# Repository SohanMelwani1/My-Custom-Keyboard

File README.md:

# My-Custom-Keyboard
My own Custom 60% Mechanical Keyboard

BOM link: https://docs.google.com/spreadsheets/d/1pmS31pF6GHp4k1bNOez-trRHEgPxX3IoW4xAfGn9qzQ/edit?gid=0#gid=0

# Features
- 3 Macros
- Anti-Ghosting
- customizable keycaps and switches
- swappable switches without needing to re-solder it
- 60% mechanical keyboard
- no screws required
- 3d printed case
- Matrix layout
- 61 keys

___

While making this I learnt How Matrix keyboards work, types of mounting of keyboards, Schematic and how to use it, PCB wiring, importing pcb to fusion and creating case, Firmware and about keyboards in general, this was my first PCB I have ever designed. I added 4 holes in each corner of the case to secure the pieces into place.

___

PCB without ground

PCB

PCB 3d view

Schematic stabilizers and mounting hole

Schematic RaspberryPi_Pico

Schematic Matrix with switches and diodes

Full schematic

Full 3d model

3d model case, plate and top frame

3d model case 

3d model plate

3d model top frame

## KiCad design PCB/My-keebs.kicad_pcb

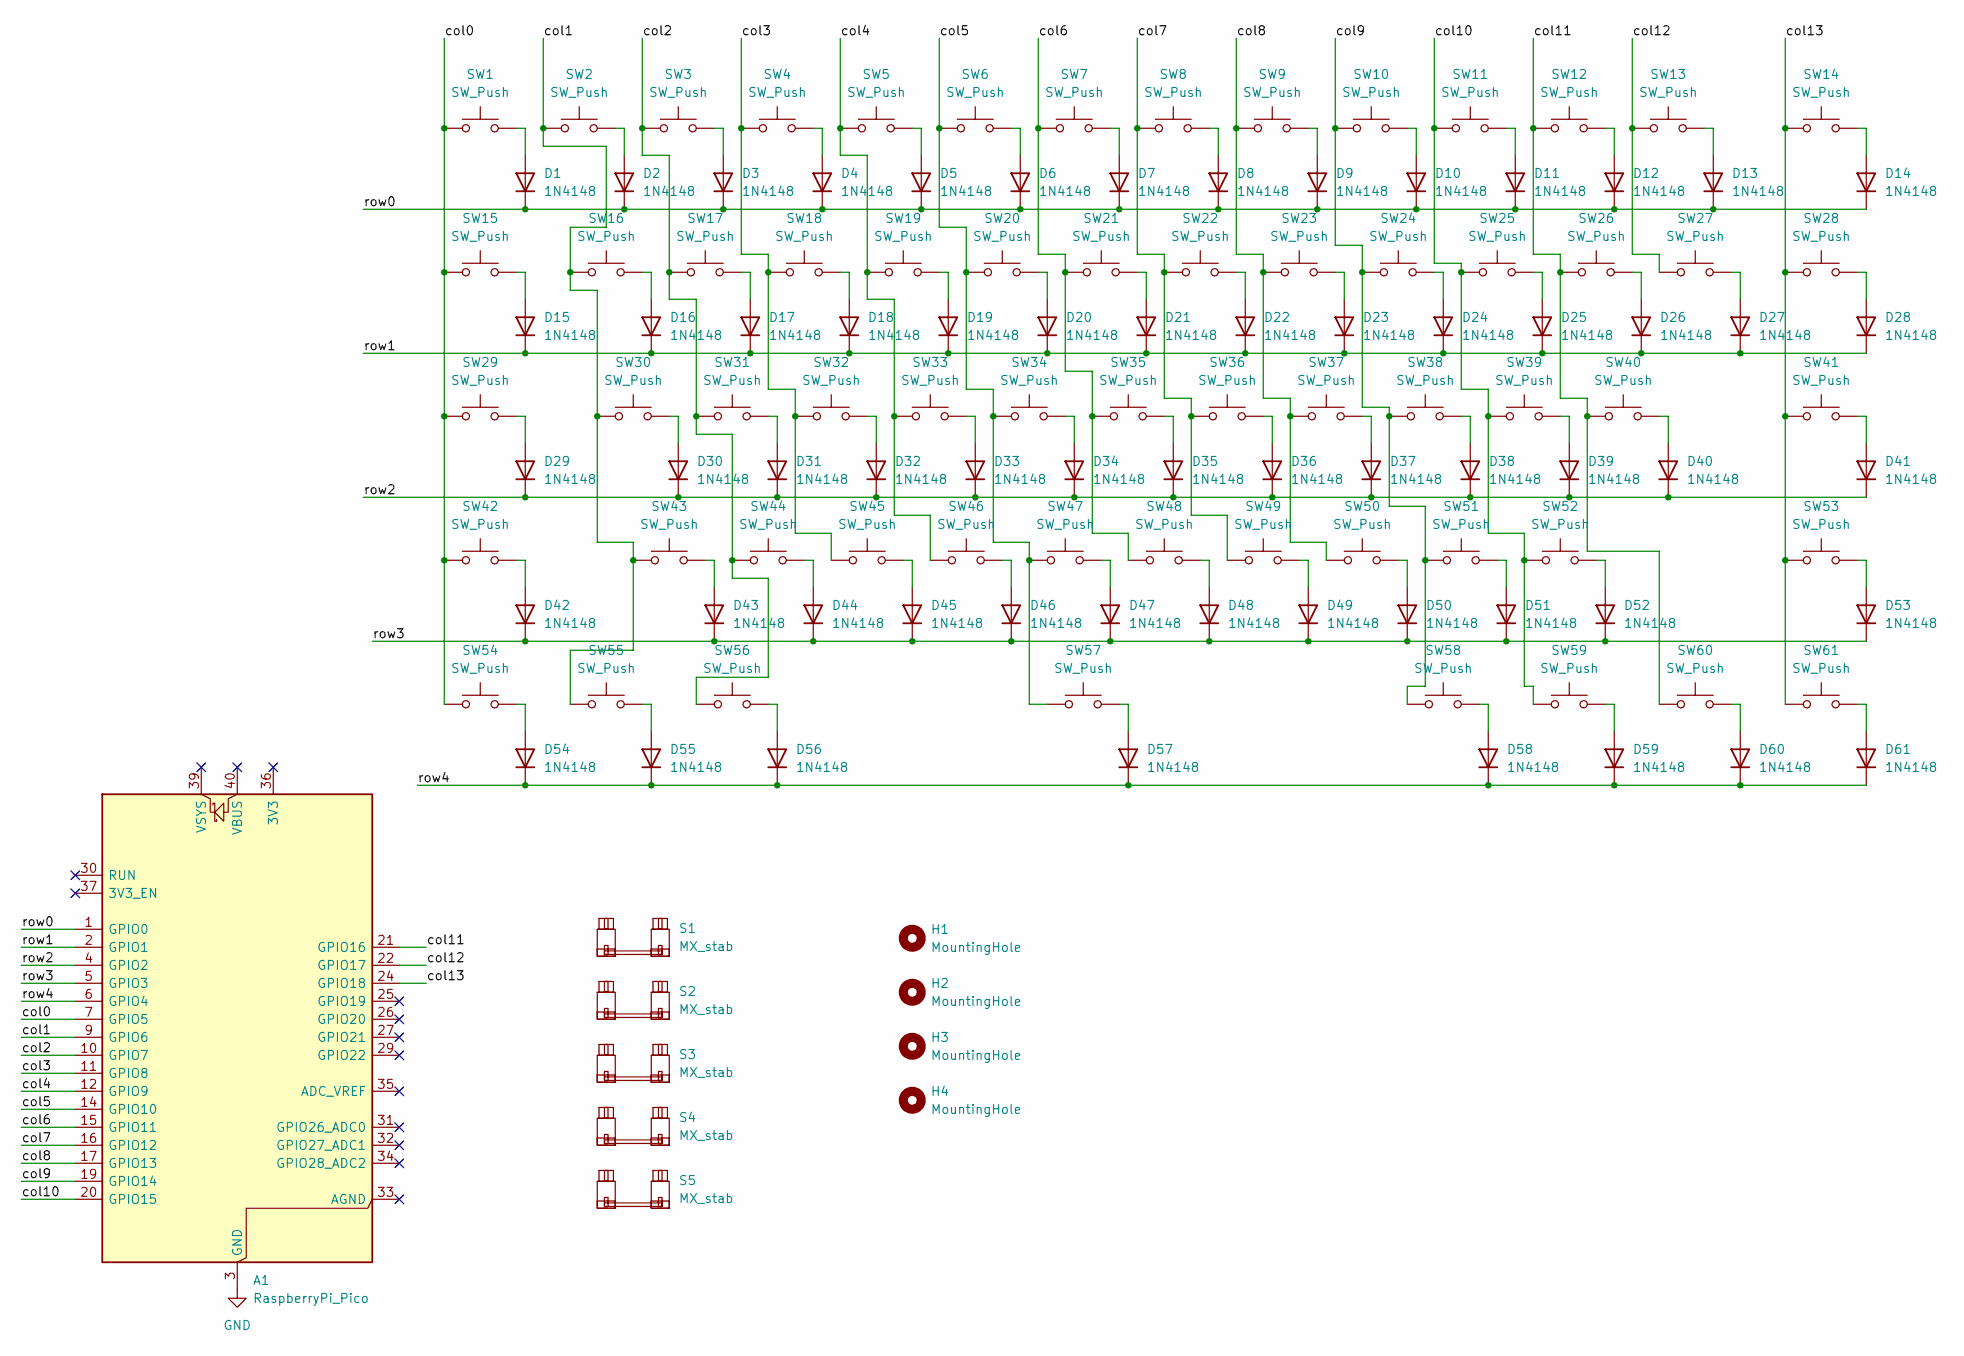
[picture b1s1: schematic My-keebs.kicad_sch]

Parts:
A1: RaspberryPi_Pico; RaspberryPi_Pico_Common_THT
D1, D2, D3, D4, D5, D6, D7, D8, D9, D10, D11, D12, D13, D14, D15, D16, D17, D18, D19, D20, D21, D22, D23, D24, D25, D26, D27, D28, D29, D30, D31, D32, D33, D34, D35, D36, D37, D38, D39, D40, D41, D42, D43, D44, D45, D46, D47, D48, D49, D50, D51, D52, D53, D54, D55, D56, D57, D58, D59, D60, D61: 1N4148; D_DO-35_SOD27_P7.62mm_Horizontal
H1, H2, H3, H4: MountingHole; MountingHole_3.2mm_M3
S1, S2, S3, S5: MX_stab; STAB_MX_2u
S4: MX_stab; STAB_MX_6.25u
SW1, SW2, SW3, SW4, SW5, SW6, SW7, SW8, SW9, SW10, SW11, SW12, SW13, SW14, SW15, SW16, SW17, SW18, SW19, SW20, SW21, SW22, SW23, SW24, SW25, SW26, SW27, SW28, SW29, SW30, SW31, SW32, SW33, SW34, SW35, SW36, SW37, SW38, SW39, SW40, SW41, SW42, SW43, SW44, SW45, SW46, SW47, SW48, SW49, SW50, SW51, SW52, SW53, SW54, SW55, SW56, SW57, SW58, SW59, SW60, SW61: SW_Push; SW_MX_1u

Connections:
/col0: A1.7 (GPIO5), SW1.1, SW15.1, SW29.1, SW42.1, SW54.1
/col1: A1.9 (GPIO6), SW2.1, SW16.1, SW30.1, SW43.1, SW55.1
/col2: A1.10 (GPIO7), SW3.1, SW17.1, SW31.1, SW44.1, SW56.1
/col3: A1.11 (GPIO8), SW4.1, SW18.1, SW32.1, SW45.1
/col4: A1.12 (GPIO9), SW5.1, SW19.1, SW33.1, SW46.1
/col5: A1.14 (GPIO10), SW6.1, SW20.1, SW34.1, SW47.1, SW57.1
/col6: A1.15 (GPIO11), SW7.1, SW21.1, SW35.1, SW48.1
/col7: A1.16 (GPIO12), SW8.1, SW22.1, SW36.1, SW49.1
/col8: A1.17 (GPIO13), SW9.1, SW23.1, SW37.1, SW50.1
/col9: A1.19 (GPIO14), SW10.1, SW24.1, SW38.1, SW51.1, SW58.1
/col10: A1.20 (GPIO15), SW11.1, SW25.1, SW39.1, SW52.1, SW59.1
/col11: A1.21 (GPIO16), SW12.1, SW26.1, SW40.1, SW60.1
/col12: A1.22 (GPIO17), SW13.1, SW27.1
/col13: A1.24 (GPIO18), SW14.1, SW28.1, SW41.1, SW53.1, SW61.1
/row0: A1.1 (GPIO0), D1.1 (K), D2.1 (K), D3.1 (K), D4.1 (K), D5.1 (K), D6.1 (K), D7.1 (K), D8.1 (K), D9.1 (K), D10.1 (K), D11.1 (K), D12.1 (K), D13.1 (K), D14.1 (K)
/row1: A1.2 (GPIO1), D15.1 (K), D16.1 (K), D17.1 (K), D18.1 (K), D19.1 (K), D20.1 (K), D21.1 (K), D22.1 (K), D23.1 (K), D24.1 (K), D25.1 (K), D26.1 (K), D27.1 (K), D28.1 (K)
/row2: A1.4 (GPIO2), D29.1 (K), D30.1 (K), D31.1 (K), D32.1 (K), D33.1 (K), D34.1 (K), D35.1 (K), D36.1 (K), D37.1 (K), D38.1 (K), D39.1 (K), D40.1 (K), D41.1 (K)
/row3: A1.5 (GPIO3), D42.1 (K), D43.1 (K), D44.1 (K), D45.1 (K), D46.1 (K), D47.1 (K), D48.1 (K), D49.1 (K), D50.1 (K), D51.1 (K), D52.1 (K), D53.1 (K)
/row4: A1.6 (GPIO4), D54.1 (K), D55.1 (K), D56.1 (K), D57.1 (K), D58.1 (K), D59.1 (K), D60.1 (K), D61.1 (K)
GND: A1.3 (GND), A1.8 (GND), A1.13 (GND), A1.18 (GND), A1.23 (GND), A1.28 (GND), A1.38 (GND)
unnamed: D1.2 (A), SW1.2
unnamed: D2.2 (A), SW2.2
unnamed: D3.2 (A), SW3.2
unnamed: D4.2 (A), SW4.2
unnamed: D5.2 (A), SW5.2
unnamed: D6.2 (A), SW6.2
unnamed: D7.2 (A), SW7.2
unnamed: D8.2 (A), SW8.2
unnamed: D9.2 (A), SW9.2
unnamed: D10.2 (A), SW10.2
unnamed: D11.2 (A), SW11.2
unnamed: D12.2 (A), SW12.2
unnamed: D13.2 (A), SW13.2
unnamed: D14.2 (A), SW14.2
unnamed: D15.2 (A), SW15.2
unnamed: D16.2 (A), SW16.2
unnamed: D17.2 (A), SW17.2
unnamed: D18.2 (A), SW18.2
unnamed: D19.2 (A), SW19.2
unnamed: D20.2 (A), SW20.2
unnamed: D21.2 (A), SW21.2
unnamed: D22.2 (A), SW22.2
unnamed: D23.2 (A), SW23.2
unnamed: D24.2 (A), SW24.2
unnamed: D25.2 (A), SW25.2
unnamed: D26.2 (A), SW26.2
unnamed: D27.2 (A), SW27.2
unnamed: D28.2 (A), SW28.2
unnamed: D29.2 (A), SW29.2
unnamed: D30.2 (A), SW30.2
unnamed: D31.2 (A), SW31.2
unnamed: D32.2 (A), SW32.2
unnamed: D33.2 (A), SW33.2
unnamed: D34.2 (A), SW34.2
unnamed: D35.2 (A), SW35.2
unnamed: D36.2 (A), SW36.2
unnamed: D37.2 (A), SW37.2
unnamed: D38.2 (A), SW38.2
unnamed: D39.2 (A), SW39.2
unnamed: D40.2 (A), SW40.2
unnamed: D41.2 (A), SW41.2
unnamed: D42.2 (A), SW42.2
unnamed: D43.2 (A), SW43.2
unnamed: D44.2 (A), SW44.2
unnamed: D45.2 (A), SW45.2
unnamed: D46.2 (A), SW46.2
unnamed: D47.2 (A), SW47.2
unnamed: D48.2 (A), SW48.2
unnamed: D49.2 (A), SW49.2
unnamed: D50.2 (A), SW50.2
unnamed: D51.2 (A), SW51.2
unnamed: D52.2 (A), SW52.2
unnamed: D53.2 (A), SW53.2
unnamed: D54.2 (A), SW54.2
unnamed: D55.2 (A), SW55.2
unnamed: D56.2 (A), SW56.2
unnamed: D57.2 (A), SW57.2
unnamed: D58.2 (A), SW58.2
unnamed: D59.2 (A), SW59.2
unnamed: D60.2 (A), SW60.2
unnamed: D61.2 (A), SW61.2

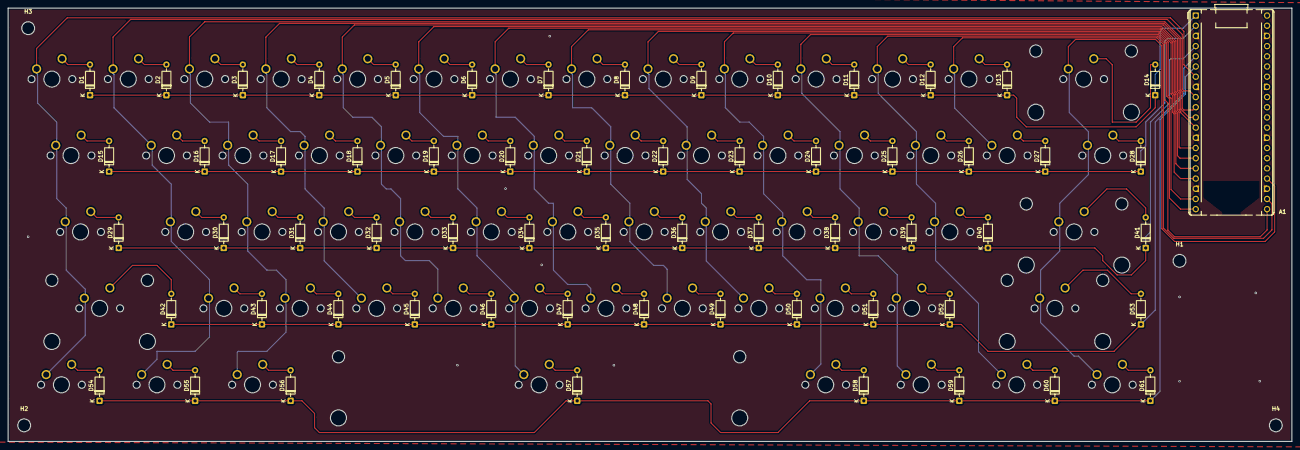
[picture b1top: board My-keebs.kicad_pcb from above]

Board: 2 copper layers, 320.0 x 108.0 mm, 132 parts (0 on the bottom side), 81 nets.
